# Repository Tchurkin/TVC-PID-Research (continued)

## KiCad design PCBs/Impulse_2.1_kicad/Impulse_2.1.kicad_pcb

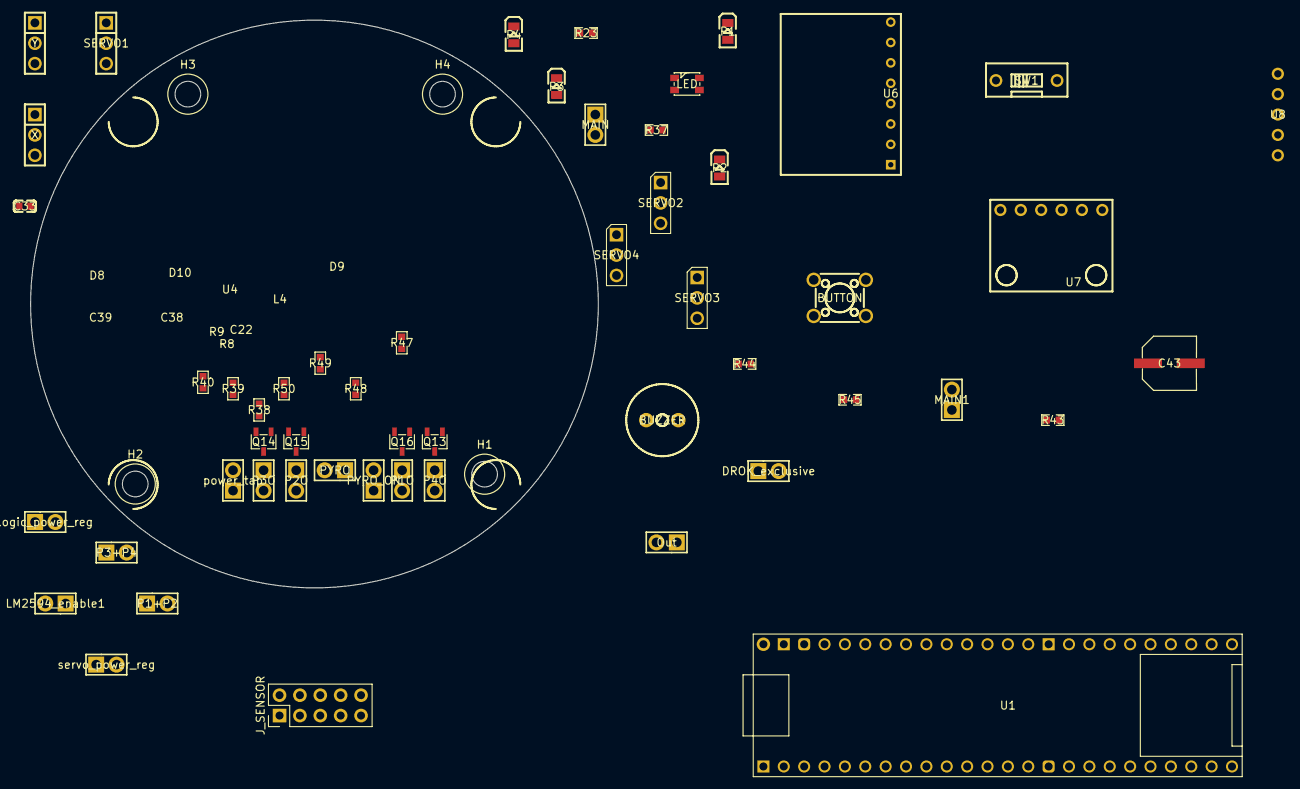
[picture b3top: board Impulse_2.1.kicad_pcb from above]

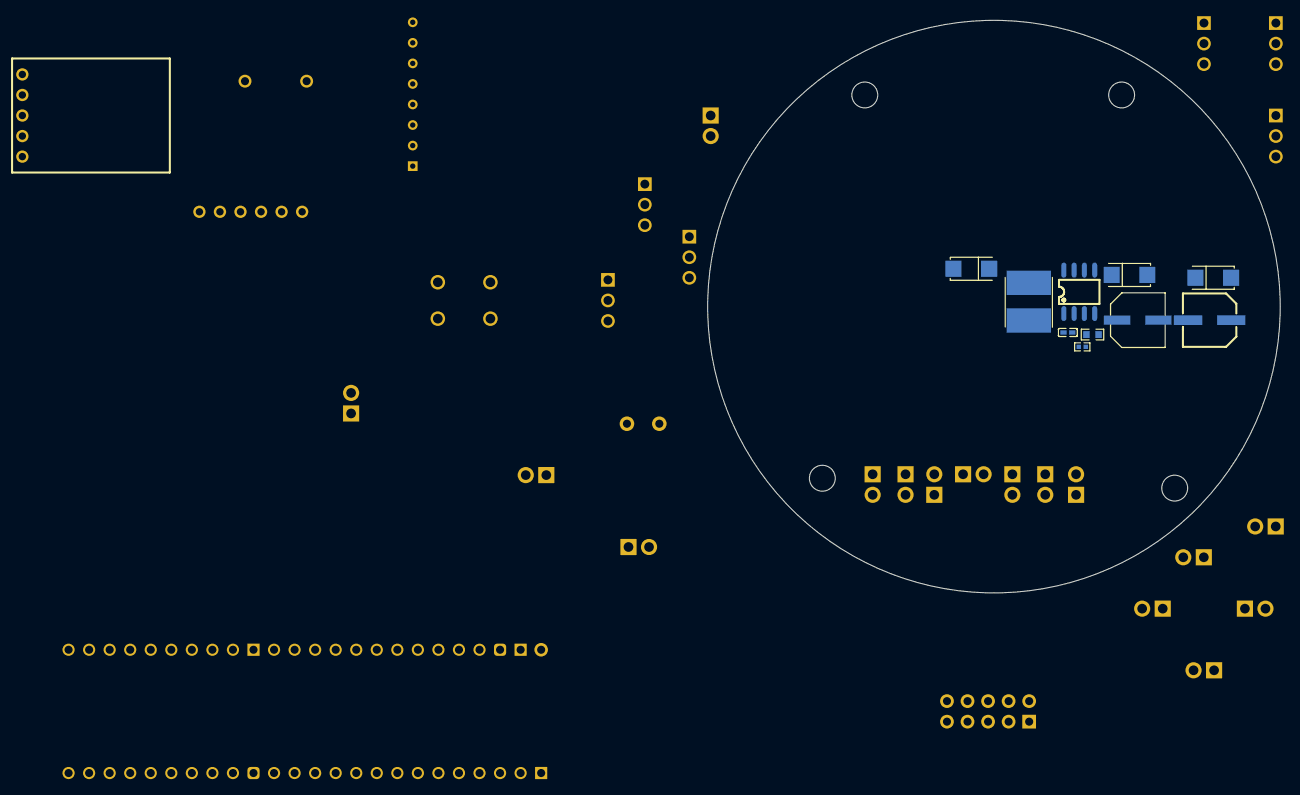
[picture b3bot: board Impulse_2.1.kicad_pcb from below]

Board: 2 copper layers, 70.8 x 70.8 mm, 67 parts (11 on the bottom side), 47 nets, no tracks yet.

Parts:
BUTTON: SW-TH_4P-L6.0-W6.0-P4.50-LS6.5
BUZZER: BUZ-TH_BD9.0-P4.00-D0.6-FD
C22: C0402
C33: C0603
C38: CAP-SMD_BD6.3-L6.6-W6.6-LS7.2-R-RD
C39: CAP-SMD_BD6.3-L6.5-W6.5-LS7.2-FD
C43: CAP-SMD_BD6.3-L6.6-W6.6-FD
D8, D9, D10: SMA_L4.3-W2.6-LS5.2-RD
DROK_exclusive: HDR-TH_2P-P2.54-V-M
H1, H2, H3, H4: MountingHole_3.2mm_M3
J_SENSOR: Header 2x5 sensor module; PinHeader_2x05_P2.54mm_Vertical
L4: IND-SMD_L5.8-W5.2
LED: LED-SMD_4P-L3.2-W2.8-LS3.5-BL-CW
LM2594_enable1: HDR-TH_2P-P2.54-V-M
MAIN, MAIN1: HDR-TH_2P-P2.54-V-M
Out: HDR-TH_2P-P2.54-V-M
P1, P2, P3, P4: LED0805-R-RD
P1+P2, P1O, P2O, P3+P4, P3O, P4O: HDR-TH_2P-P2.54-V-M
PYRO: HDR-TH_2P-P2.54-V-M
PYRO_ON: HDR-TH_2P-P2.54-V-M
Q13, Q14, Q15, Q16: SOT-23-3_L2.9-W1.6-P1.90-LS2.8-BR
R8: R0402
R9, R23, R37, R38, R39, R40, R43, R44, R45, R47, R48, R49, R50: R0603
SERVO1, SERVO2, SERVO3, SERVO4: HDR-TH_3P-P2.54-V-M
SW1: SW-TH_DSWB01LHGET
U1: TEENSY41
U4: SOP-8_L4.9-W3.9-P1.27-LS6.0-BL
U6: MPU-6050 MODULE
U7: BMP280
U8: BUCK CONVERTER-DROK
X: HDR-TH_3P-P2.54-V-M
Y: HDR-TH_3P-P2.54-V-M
logic_power_reg: HDR-TH_2P-P2.54-V-M
power_tap: HDR-TH_2P-P2.54-V-M
servo_power_reg: HDR-TH_2P-P2.54-V-M

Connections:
3.3V: BUTTON.1, J_SENSOR.1, LED.1, MAIN1.1, U1.3V3-1, U1.3V3-3, U6.1, U7.1
5V-CLEAN: C33.2, D8.1, DROK_exclusive.1, U1.VIN
5V-DIRTY: C43.1, D9.1, DROK_exclusive.2, SERVO1.2, SERVO2.2, SERVO3.2, SERVO4.2, X.2, Y.2
7.4V: P1O.2, P2O.2, P3O.2, P4O.2, PYRO_ON.1, power_tap.1
$1N14222: LED.3, R39.1
$1N14265: LED.4, R40.1
$1N14307: LED.2, R38.2
$1N14383: BUTTON.4, R23.2
$1N33864: C22.1, R8.1, R9.1, U4.4
$1N33870: D10.1, L4.1, U4.8
$1N42243: P1O.1, Q16.3, R37.1
$1N42245: P1.1, R37.2
$1N42393: P2O.1, Q15.3, R43.1
$1N42395: P2.1, R43.2
$1N42562: P3.1, R44.2
$1N49822: D9.2, U8.1, servo_power_reg.2
$1N50177: PYRO.1, PYRO_ON.2
$1N50225: MAIN.1, SW1.1
$1N50240: C39.1, SW1.2, U4.7, U8.4, logic_power_reg.1, servo_power_reg.1
$1N52582: D8.2, LM2594_enable1.2, logic_power_reg.2
$1N52591: C22.2, C38.1, L4.2, LM2594_enable1.1, R8.2
$1N56605: P4.1, R45.1
$1N56609: P4O.1, Q13.3, R45.2
$1N56715: P3O.1, Q14.3, R44.1
BUTTON: BUTTON.3, U1.14-A0/TX3/SPDIF_OUT
BUZZER: BUZZER.1, U1.13-SCK/LED
B_LED: R38.1, U1.8-TX2/IN2
CS_IMU: J_SENSOR.6, U1.0-RX1/CS1/CRX2
GND: BUZZER.2, C33.1, C38.2, C39.2, C43.2, D10.2, J_SENSOR.2, J_SENSOR.10, MAIN.2, MAIN1.2, P1.2, P2.2, P3.2, P4.2, PYRO.2, Q13.2, Q14.2, Q15.2, Q16.2, R9.2, R23.1, R47.2, R48.2, R49.2, R50.2, SERVO1.3, SERVO2.3, SERVO3.3, SERVO4.3, U1.GND1, U1.GND3, U1.GND6, U4.5, U4.6, U6.2, U7.2, U8.2, U8.3, X.3, Y.3, power_tap.2
G_LED: R39.2, U1.7-RX2/OUT1A
INT_IMU: J_SENSOR.7, U1.2-OUT2
MISO: J_SENSOR.5, U1.1-TX1/MISO1/CTX2
MOSI: J_SENSOR.4, U1.26-A12/MOSI1
PYRO1: P1+P2.1, Q16.1, R50.1, U1.9-OUT1C
PYRO2: P1+P2.2, Q15.1, R49.1, U1.10-CS\MQSR
PYRO3: P3+P4.1, Q14.1, R48.1, U1.11-MOSI/CTX1
PYRO4: P3+P4.2, Q13.1, R47.1, U1.12-MISO/MQSL
R_LED: R40.2, U1.6-OUT1D
SCK: J_SENSOR.3, U1.27-A13/SCK1
SCL: J_SENSOR.9, Out.2, U1.19-A5/SCL0, U6.3, U6.6, U7.3
SDA: J_SENSOR.8, Out.1, U1.18-A4/SDA0, U6.4, U6.5, U7.4
SERVO1: SERVO1.1, U1.5-IN2
SERVO2: SERVO2.1, U1.28-RX7
SERVO3: SERVO3.1, U1.29-TX7
SERVO4: SERVO4.1, U1.25-A11/RX6/SDA2
SERVOX: U1.3-LRCLK2, X.1
SERVOY: U1.4-BCLK2, Y.1

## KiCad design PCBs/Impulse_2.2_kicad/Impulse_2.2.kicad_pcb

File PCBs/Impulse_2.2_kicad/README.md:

# Impulse 2.2 — native KiCad rebuild

Clean-room rebuild of Impulse 2.1 (EasyEDA import) on **native KiCad libraries**. Same wiring,
same placement, same board outline — none of the conversion baggage (stranded silk, broken
annotation, pad-name mismatches).

- **Netlist verified identical** to Impulse 2.1 (183 connections, checked three ways: old PCB →
  new PCB → KiCad-exported schematic netlist). ERC: 0 violations.
- **Forward/back annotation works** — schematic and PCB are properly UUID-linked. "Update PCB
  from Schematic" is safe here (unlike 2.1).
- Unrouted (as was 2.1): DRC shows only ratsnest items + 6 courtyard overlaps from the packed
  import placement — re-place/route freely, silk moves with parts.
- Custom parts live in `Impulse22.pretty` / `Impulse22.kicad_sym` (Teensy 4.1 48-pin header
  footprint, 9mm/4.0mm-pitch buzzer).

## Deliberate changes vs 2.1
- Net renames for readability: `$1N50240`→`VBAT_SW`, `$1N52591`→`BUCK_5V`, `$1N33864`→`BUCK_FB`,
  `$1N33870`→`BUCK_SW`, `$1N50177`→`PYRO_ARM`, pyro channels→`PYROn_OUT`/`PYROn_LED`,
  RGB→`RGB_R/G/B`, etc.
- Ref renames (KiCad annotation needs a trailing digit): `X`→`X1`, `Y`→`Y1`, `PYRO`→`PYRO1`,
  `Out`→`OUT1`, `MAIN`→`BAT_MAIN1`, `MAIN1`→`AUX_3V3_1`, `LED`→`LED1`, `BUTTON`→`BUTTON1`,
  `BUZZER`→`BUZZER1`, `P1O`→`P1O1`, headers get a `1` suffix.
- `BUTTON` net merge: old nets `BUTTON` + `$1N14383` were one node through the switch's
  internally-bonded pins 3/4 — now a single `BUTTON` net on SW_PUSH pad pair 2.
- Teensy pads renamed to plain `0`–`41`, `VIN`, `3V3_1/2`, `GND1-3`.
- LED footprint pad numbering follows KiCad convention (1=K, 2=A — polarity preserved from 2.1).
- U4/LM2594 pinout verified against datasheet (4=FB, 7=VIN, 8=OUT; 5/6 both to GND).

## Schematic drawing style
The schematic **reproduces the hand-drawn Impulse 2.1 layout** — the 6 subsystem boxes and their
titles ("Voltage Regulator…", "Pyros and continuity check", "UI peripherals", "Servos (9 gram)",
"External Sensor Board", "Backup Sensors"), the original wires, and label placement — rebuilt with
native symbols. Where a native symbol's pin lands slightly off the old EasyEDA pin, a short stub
wire bridges it; only genuine cross-subsystem signals use labels (as in your original). Netlist
verified **byte-for-byte identical to the PCB** (183 connections, checked against KiCad's own
exporter). ERC: 0 errors, 67 warnings — all cosmetic (off-grid endpoints from the EasyEDA sub-grid,
lib-symbol-cache notes), same class the 2.1 import had.

Generators:
- `_gen_pcb.py` — reads `../Impulse_2.1_kicad/_inventory.json`, emits the native PCB.
- `_gen_sch2.py` — reads the PCB + the old schematic geometry, emits the layout-preserving sheet.
  (`_gen_sch.py` is the earlier grid-layout version, kept for reference.)
- `_patch_labels.py` — run AFTER `_gen_sch2.py`; uses KiCad's netlist as ground truth to drop a
  label on any pin a sub-grid stub missed (currently the 3 RGB-resistor pins).
- `_sym_uuids.json` links schematic symbols to PCB footprints; `_pin_nets.json` feeds the patcher.

Regen recipe: `python _gen_pcb.py && python _gen_sch2.py && python _patch_labels.py`

## Power redesign (2026-07-02)
Replaced the 150 kHz LM2594 circuit + DROK module + OR-diodes + 5 selector jumpers with two
1.1 MHz synchronous bucks (`_redesign_sch.py` / `_redesign_pcb.py`):
- **U2 = AP63205WU-7** (5 V / 2 A, TSOT-23-6) → `5V-CLEAN` (Teensy + sensors)
- **U3 = AP63305WU-7** (5 V / 3 A, same family/pinout — *verify pinout vs datasheet before fab*)
  → `SERVO_EN1` jumper → `5V-DIRTY` (servos)
- Each: 10 µF in (C1/C2), 100 nF BST (C3/C4), 6.8/4.7 µH SRN6045 (L1/L2), 2×22 µF out (C5–C8).
- **C10 = 220 µF** bulk on the pyro 7.4 V rail (was missing entirely).
- Jumpers kept: `PYRO_ON1` (pyro arming), `SERVO_EN1` (servo disable), SW1 master switch.
  Removed: `DROK_exclusive1` (bridged clean↔dirty!), `LM2594_enable1`, `logic_power_reg1`,
  `servo_power_reg1`, `power_tap1`.
- Net `Net-(SW1-B)` → `VBAT`. ERC 0/0; sch==pcb verified (204 connections).

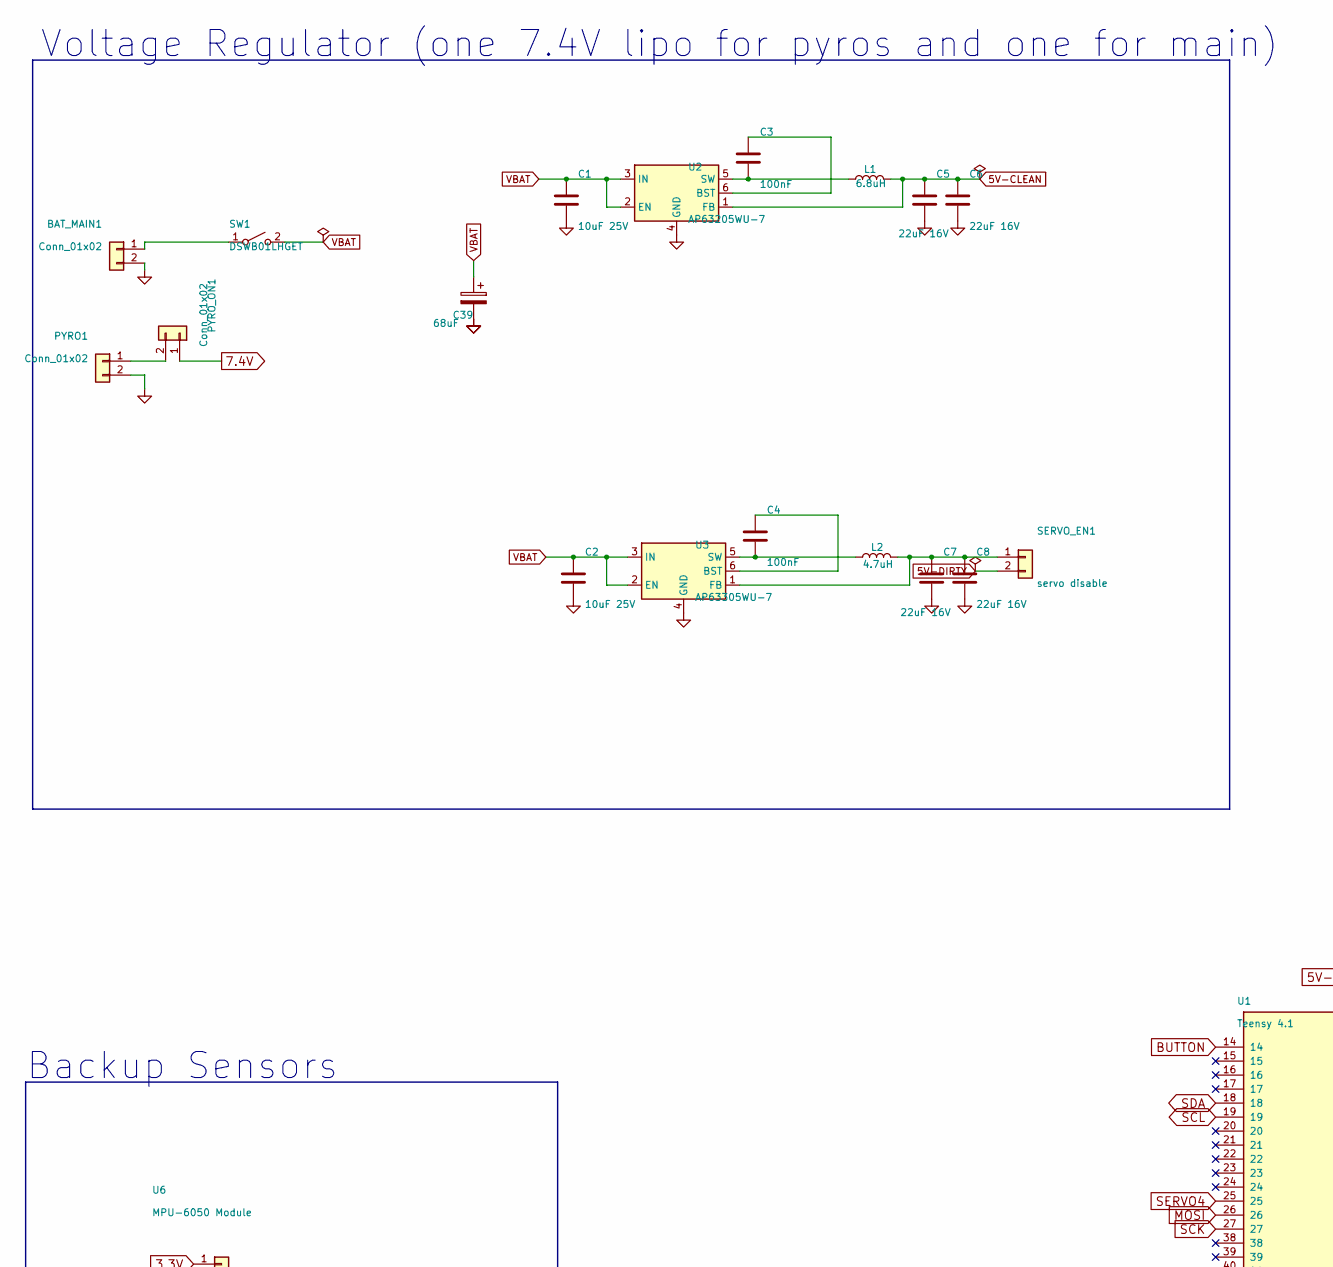
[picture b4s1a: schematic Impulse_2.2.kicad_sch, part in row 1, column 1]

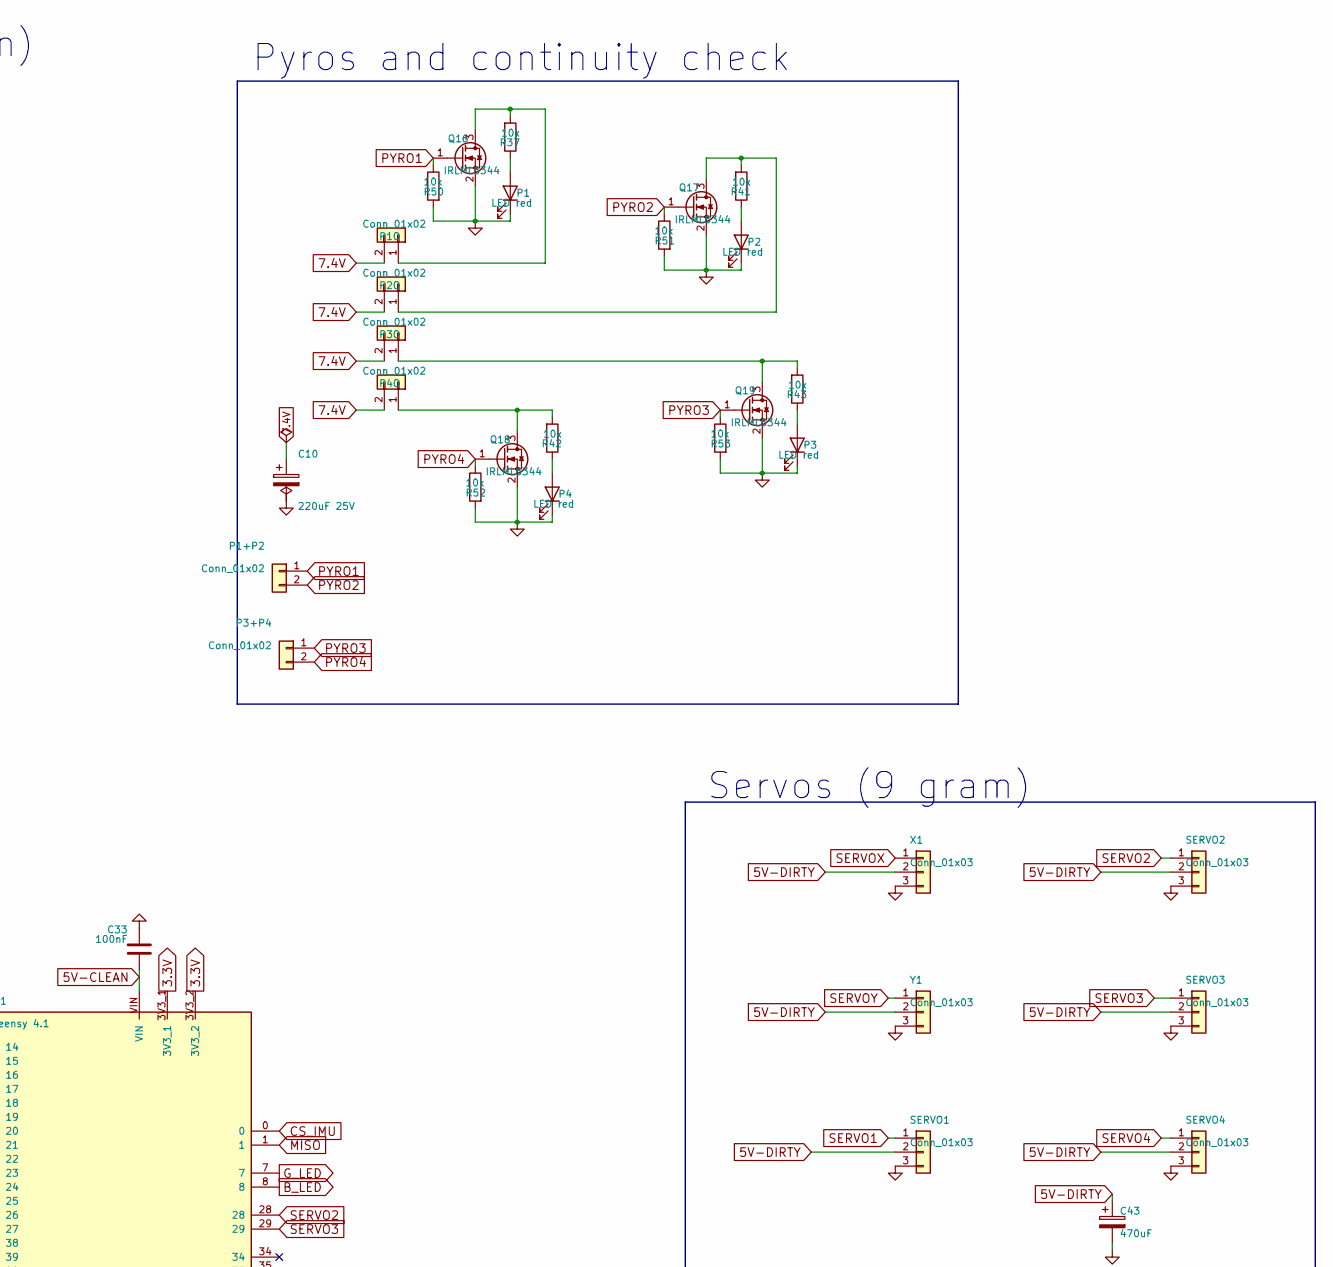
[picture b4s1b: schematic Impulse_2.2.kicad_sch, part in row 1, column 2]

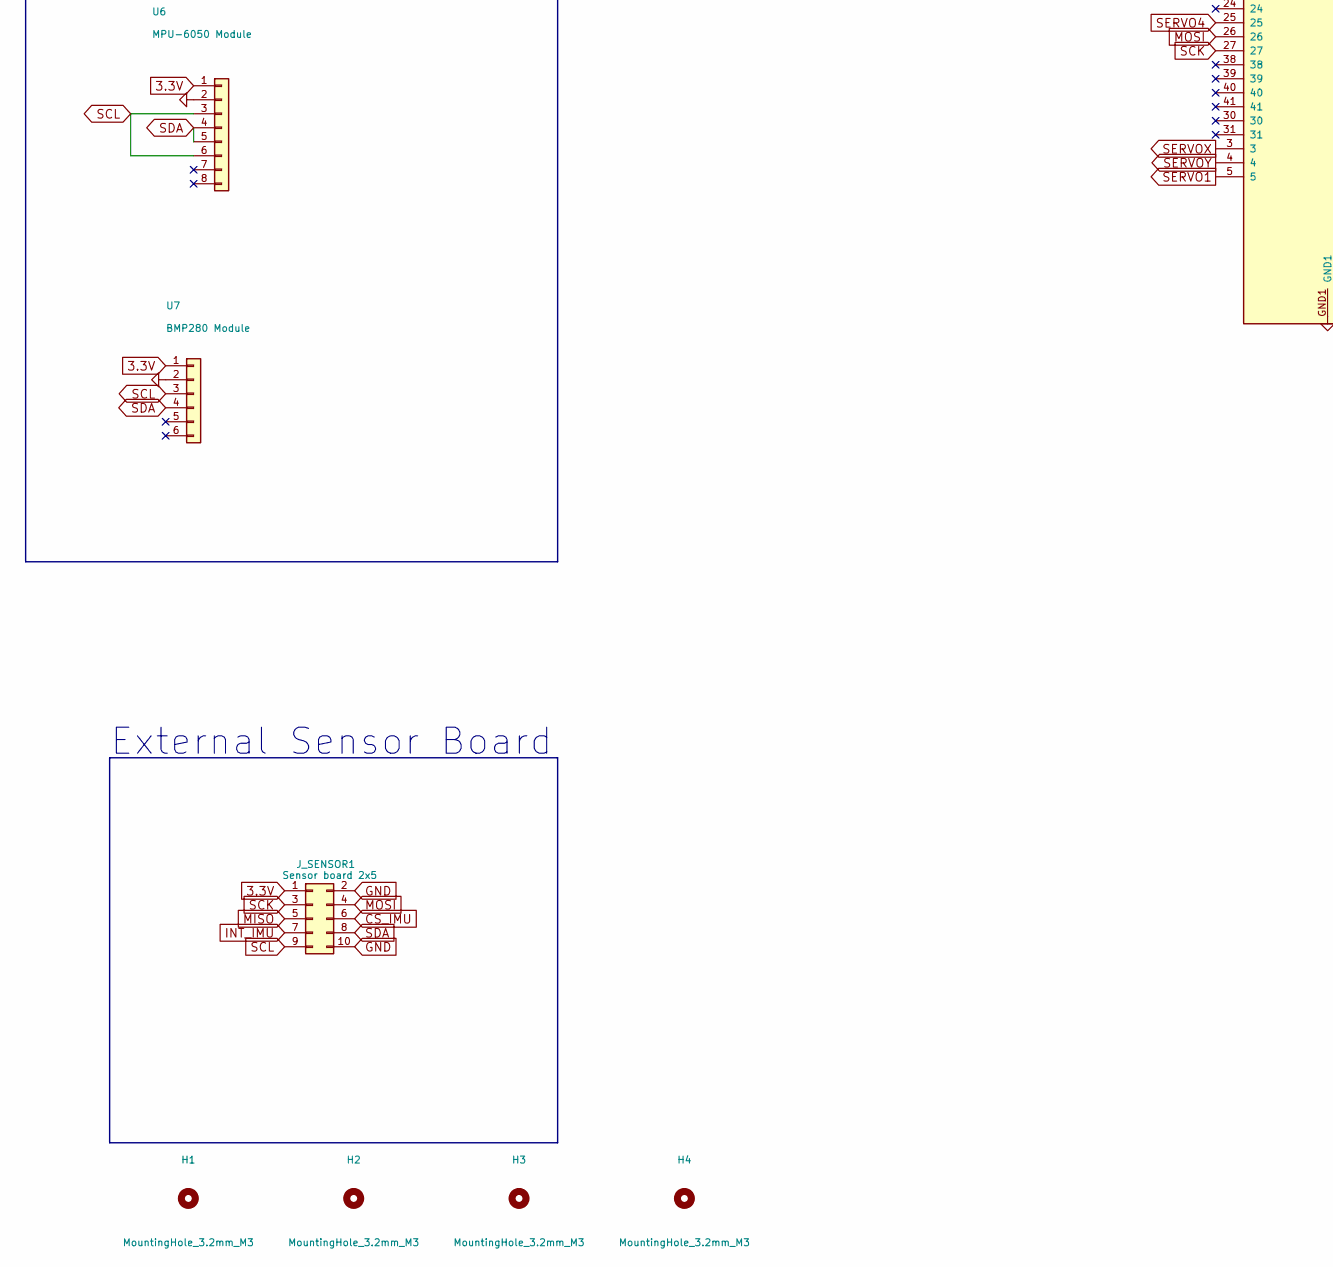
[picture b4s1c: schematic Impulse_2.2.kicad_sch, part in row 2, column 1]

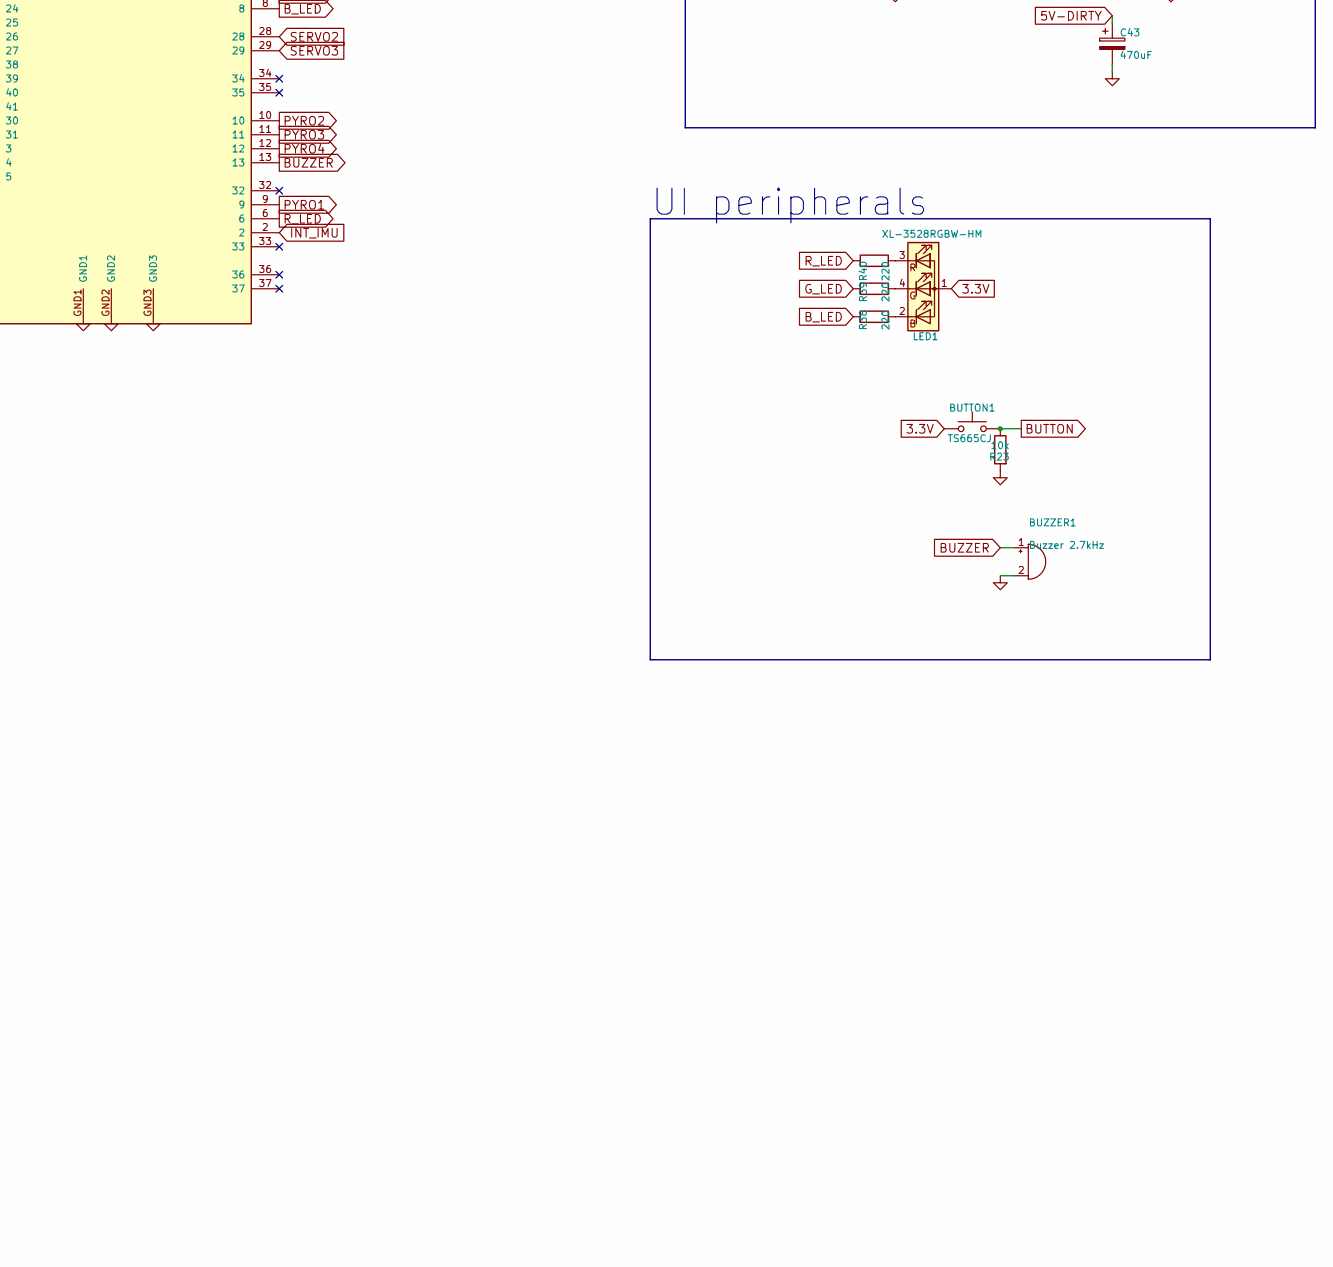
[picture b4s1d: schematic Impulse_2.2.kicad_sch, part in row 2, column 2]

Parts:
BAT_MAIN1: Conn_01x02; PinHeader_1x02_P2.54mm_Vertical
BUTTON1: TS665CJ; SW_PUSH_6mm
BUZZER1: Buzzer 2.7kHz; Buzzer_D9.0mm_P4.00mm
C1, C2: 10uF 25V; C_1206_3216Metric
C3, C4, C33: 100nF; C_0603_1608Metric
C5, C6, C7, C8: 22uF 16V; C_1206_3216Metric
C10: 220uF 25V; CP_Elec_8x10
C39: 68uF; CP_Elec_6.3x7.7
C43: 470uF; CP_Elec_6.3x7.7
H1, H2, H3, H4: MountingHole_3.2mm_M3
J_SENSOR1: Sensor board 2x5; PinHeader_2x05_P2.54mm_Vertical
L1: 6.8uH; L_Bourns_SRN6045TA
L2: 4.7uH; L_Bourns_SRN6045TA
LED1: XL-3528RGBW-HM; LED_RGB_Wuerth-PLCC4_3.2x2.8mm_150141M173100
P1, P2, P3, P4: LED red; LED_0805_2012Metric
P1+P2, P1O, P2O, P3+P4, P3O, P4O: Conn_01x02; PinHeader_1x02_P2.54mm_Vertical
PYRO1: Conn_01x02; PinHeader_1x02_P2.54mm_Vertical
PYRO_ON1: Conn_01x02; PinHeader_1x02_P2.54mm_Vertical
Q16, Q17, Q18, Q19: IRLML6344; SOT-23
R23, R37, R41, R42, R43, R50, R51, R52, R53: 10k; R_0603_1608Metric
R38, R39, R40: 220; R_0603_1608Metric
SERVO1, SERVO2, SERVO3, SERVO4: Conn_01x03; PinHeader_1x03_P2.54mm_Vertical
SERVO_EN1: servo disable; PinHeader_1x02_P2.54mm_Vertical
SW1: DSWB01LHGET; SW_DIP_SPSTx01_Slide_6.7x4.1mm_W7.62mm_P2.54mm_LowProfile
U1: Teensy 4.1; TEENSY41
U2: AP63205WU-7; TSOT-23-6
U3: AP63305WU-7; TSOT-23-6
U6: MPU-6050 Module; PinHeader_1x08_P2.54mm_Vertical
U7: BMP280 Module; PinHeader_1x06_P2.54mm_Vertical
X1: Conn_01x03; PinHeader_1x03_P2.54mm_Vertical
Y1: Conn_01x03; PinHeader_1x03_P2.54mm_Vertical

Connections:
3.3V: BUTTON1.1, J_SENSOR1.1, LED1.1 (A), U1.3V3_1, U1.3V3_2, U6.1, U7.1
5V-CLEAN: C5.1, C6.1, C33.2, L1.2, U1.VIN, U2.1 (FB)
5V-DIRTY: C43.1, SERVO1.2, SERVO2.2, SERVO3.2, SERVO4.2, SERVO_EN1.2, X1.2, Y1.2
7.4V: C10.1, P1O.2, P2O.2, P3O.2, P4O.2, PYRO_ON1.1
BUTTON: BUTTON1.2, R23.1, U1.14
BUZZER: BUZZER1.1 (+), U1.13
B_LED: R38.1, U1.8
CS_IMU: J_SENSOR1.6, U1.0
GND: BAT_MAIN1.2, BUZZER1.2 (-), C1.2, C2.2, C5.2, C6.2, C7.2, C8.2, C10.2, C33.1, C39.2, C43.2, J_SENSOR1.2, J_SENSOR1.10, P1.1 (K), P2.1 (K), P3.1 (K), P4.1 (K), PYRO1.2, Q16.2 (S), Q17.2 (S), Q18.2 (S), Q19.2 (S), R23.2, R50.2, R51.2, R52.2, R53.2, SERVO1.3, SERVO2.3, SERVO3.3, SERVO4.3, U1.GND1, U1.GND2, U1.GND3, U2.4 (GND), U3.4 (GND), U6.2, U7.2, X1.3, Y1.3
G_LED: R39.1, U1.7
INT_IMU: J_SENSOR1.7, U1.2
MISO: J_SENSOR1.5, U1.1
MOSI: J_SENSOR1.4, U1.26
unnamed: BAT_MAIN1.1, SW1.1 (A)
unnamed: LED1.2 (BK), R38.2
unnamed: LED1.4 (GK), R39.2
unnamed: LED1.3 (RK), R40.2
unnamed: P1.2 (A), R37.1
unnamed: P1O.1, Q16.3 (D), R37.2
unnamed: P2.2 (A), R41.1
unnamed: P2O.1, Q17.3 (D), R41.2
unnamed: P3.2 (A), R43.1
unnamed: P3O.1, Q19.3 (D), R43.2
unnamed: P4.2 (A), R42.1
unnamed: P4O.1, Q18.3 (D), R42.2
unnamed: PYRO1.1, PYRO_ON1.2
unnamed: C7.1, C8.1, L2.2, SERVO_EN1.1, U3.1 (FB)
unnamed: C3.1, U2.6 (BST)
unnamed: C3.2, L1.1, U2.5 (SW)
unnamed: C4.1, U3.6 (BST)
unnamed: C4.2, L2.1, U3.5 (SW)
PYRO1: P1+P2.1, Q16.1 (G), R50.1, U1.9
PYRO2: P1+P2.2, Q17.1 (G), R51.1, U1.10
PYRO3: P3+P4.1, Q19.1 (G), R53.1, U1.11
PYRO4: P3+P4.2, Q18.1 (G), R52.1, U1.12
R_LED: R40.1, U1.6
SCK: J_SENSOR1.3, U1.27
SCL: J_SENSOR1.9, U1.19, U6.3, U6.6, U7.3
SDA: J_SENSOR1.8, U1.18, U6.4, U6.5, U7.4
SERVO1: SERVO1.1, U1.5
SERVO2: SERVO2.1, U1.28
SERVO3: SERVO3.1, U1.29
SERVO4: SERVO4.1, U1.25
SERVOX: U1.3, X1.1
SERVOY: U1.4, Y1.1
VBAT: C1.1, C2.1, C39.1, SW1.2 (B), U2.2 (EN), U2.3 (IN), U3.2 (EN), U3.3 (IN)

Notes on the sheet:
Pyros and continuity check
Voltage Regulator (one 7.4V lipo for pyros and one for main)
UI peripherals
Servos (9 gram)
External Sensor Board
Backup Sensors

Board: 2 copper layers, 64 parts (13 on the bottom side), 46 nets, no tracks yet.

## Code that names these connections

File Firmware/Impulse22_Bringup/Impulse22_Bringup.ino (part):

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
  Pin map verified pad-by-pad against PCBs/Impulse_2.2_kicad/Impulse_2.2.kicad_pcb
  (2026-08-12). It is NOT the same as the old Sysiphus sketches: those use
  Serial1 for GPS (= pins 0/1 = CS_IMU/MISO here) and servo pin 2 (= INT_IMU).

  SENSORS
    Sensor board, SPI1 @ MOSI 26 / MISO 1 / SCK 27:
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#include <Adafruit_BMP280.h>

// ── Impulse 2.2 pin map ──────────────────────────────────────────────────────
constexpr int PIN_CS_IMU    = 0;    // SPI1 CS  -> ICM-42688-P
constexpr int PIN_INT_IMU   = 2;    // ICM-42688-P INT1
constexpr int PIN_RLED      = 6;    // RGB LED1 is COMMON ANODE to 5V-CLEAN:
constexpr int PIN_GLED      = 7;    //   drive LOW = on, HIGH = off
constexpr int PIN_BLED      = 8;
constexpr int PIN_PYRO[4]   = {9, 10, 11, 12};
constexpr int PIN_BUZZER    = 13;   // gate of Q22, active HIGH
constexpr int PIN_BUTTON    = 14;   // 10k pulldown R23, pressed = HIGH
constexpr int PIN_CS_BARO   = 15;   // SPI1 CS  -> DPS310
constexpr int PIN_GPS_PPS   = 20;
constexpr int PIN_VBAT_SENSE     = 21;
constexpr int PIN_SERVO_V_SENSE  = 22;
constexpr int PIN_PYRO_V_SENSE   = 23;
constexpr int PIN_MOSI1     = 26;
constexpr int PIN_SCK1      = 27;
constexpr int PIN_MISO1     = 1;
constexpr int PIN_SENS_DET  = 32;   // LOW = sensor-board harness present

#define GPS_SERIAL Serial4          // NOT Serial1 — pins 0/1 are CS_IMU/MISO
constexpr uint32_t GPS_BAUD = 9600;

// Divider ratios from the schematic: Vrail = Vpin / ratio
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  digitalWrite(PIN_GLED, !g);
  digitalWrite(PIN_BLED, !b);
}
void beep(int freq, int dur) { tone(PIN_BUZZER, freq); delay(dur); noTone(PIN_BUZZER); }

// Returns 0 = not pressed, 1 = short press, 2 = long press (>1 s)
int readButton() {
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//  ICM-42688-P
// ─────────────────────────────────────────────────────────────────────────────
bool icmBegin() {
  spiWriteReg(PIN_CS_IMU, ICM_SPI, ICM_DEVICE_CONFIG, 0x01);   // soft reset
  delay(5);

  uint8_t who = spiReadReg(PIN_CS_IMU, ICM_SPI, ICM_WHO_AM_I);
  if (who != ICM_WHOAMI_EXPECT) {
    snprintf(diag, sizeof diag, "WHO_AM_I = 0x%02X, expected 0x47%s", who,
             who == 0xFF ? "  (MISO floating / not connected?)"
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
  // Pin 9 of the LGA is unused here; lock the interface to SPI so a floating
  // I2C pad can never put the part into I2C mode mid-flight.
  uint8_t intf = spiReadReg(PIN_CS_IMU, ICM_SPI, ICM_INTF_CONFIG0);
  spiWriteReg(PIN_CS_IMU, ICM_SPI, ICM_INTF_CONFIG0, (intf & 0xFC) | 0x03);  // UI_SIFS_CFG = disable I2C

  spiWriteReg(PIN_CS_IMU, ICM_SPI, ICM_GYRO_CONFIG0,  (0x00 << 5) | 0x06);   // ±2000 dps, 1 kHz
  spiWriteReg(PIN_CS_IMU, ICM_SPI, ICM_ACCEL_CONFIG0, (0x00 << 5) | 0x06);   // ±16 g,     1 kHz
  spiWriteReg(PIN_CS_IMU, ICM_SPI, ICM_PWR_MGMT0, 0x0F);                     // gyro + accel low-noise
  delay(50);                                                                 // gyro start-up
  return true;
}
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// ax/ay/az in g, gx/gy/gz in dps, temp in degC
void icmRead(float& ax, float& ay, float& az, float& gx, float& gy, float& gz, float& tempC) {
  uint8_t b[14];
  spiReadBurst(PIN_CS_IMU, ICM_SPI, ICM_TEMP_DATA1, b, 14);
  int16_t t  = (int16_t)((b[0]  << 8) | b[1]);
  int16_t rx = (int16_t)((b[2]  << 8) | b[3]);
  int16_t ry = (int16_t)((b[4]  << 8) | b[5]);
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//  DPS310
// ─────────────────────────────────────────────────────────────────────────────
bool dpsBegin() {
  spiWriteReg(PIN_CS_BARO, DPS_SPI, DPS_RESET, 0x89);          // soft reset
  delay(50);

  uint8_t id = spiReadReg(PIN_CS_BARO, DPS_SPI, DPS_PROD_ID);
  if (id != DPS_ID_EXPECT) {
    snprintf(diag, sizeof diag, "PROD_ID = 0x%02X, expected 0x10%s", id,
             (id == 0xFF || id == 0x00) ? "  (check CS_BARO, harness pin 5)" : "");
    return false;
  }

  // Wait for the trim/coefficients to load out of OTP.
  uint32_t t0 = millis();
  while (!(spiReadReg(PIN_CS_BARO, DPS_SPI, DPS_MEAS_CFG) & 0xC0)) {   // SENSOR_RDY | COEF_RDY
    if (millis() - t0 > 500) {
      snprintf(diag, sizeof diag, "timeout waiting for SENSOR_RDY|COEF_RDY");
      return false;
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
  // Infineon errata workaround: the OTP read must be re-triggered once after
  // reset or the temperature coefficients come back wrong on some lots.
  spiWriteReg(PIN_CS_BARO, DPS_SPI, 0x0E, 0xA5);
  spiWriteReg(PIN_CS_BARO, DPS_SPI, 0x0F, 0x96);
  spiWriteReg(PIN_CS_BARO, DPS_SPI, 0x62, 0x02);
  spiWriteReg(PIN_CS_BARO, DPS_SPI, 0x0E, 0x00);
  spiWriteReg(PIN_CS_BARO, DPS_SPI, 0x0F, 0x00);

  uint8_t c[18];
  spiReadBurst(PIN_CS_BARO, DPS_SPI, DPS_COEF, c, 18);
  dpsCoef.c0  = signExtend(((uint32_t)c[0] << 4) | (c[1] >> 4), 12);
  dpsCoef.c1  = signExtend((((uint32_t)c[1] & 0x0F) << 8) | c[2], 12);
  dpsCoef.c00 = signExtend(((uint32_t)c[3] << 12) | ((uint32_t)c[4] << 4) | (c[5] >> 4), 20);
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  dpsCoef.c30 = signExtend(((uint32_t)c[16] << 8) | c[17], 16);

  // TMP_EXT must match the source the coefficients were trimmed against.
  uint8_t srce = spiReadReg(PIN_CS_BARO, DPS_SPI, DPS_COEF_SRCE) & 0x80;
  spiWriteReg(PIN_CS_BARO, DPS_SPI, DPS_PRS_CFG, 0x53);          // 32 Hz, 8x oversample
  spiWriteReg(PIN_CS_BARO, DPS_SPI, DPS_TMP_CFG, srce | 0x50);   // 32 Hz, 1x oversample
  spiWriteReg(PIN_CS_BARO, DPS_SPI, DPS_CFG_REG, 0x00);          // no shift needed at <=8x
  spiWriteReg(PIN_CS_BARO, DPS_SPI, DPS_MEAS_CFG, 0x07);         // continuous pressure + temp
  delay(50);
  return true;
}

void dpsRead(float& hPa, float& tempC, float& altM) {
  uint8_t b[6];
  spiReadBurst(PIN_CS_BARO, DPS_SPI, DPS_PSR_B2, b, 6);
  int32_t praw = signExtend(((uint32_t)b[0] << 16) | ((uint32_t)b[1] << 8) | b[2], 24);
  int32_t traw = signExtend(((uint32_t)b[3] << 16) | ((uint32_t)b[4] << 8) | b[5], 24);

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// WHO_AM_I answering — so they look present while streaming sentinel values.
// Detect the recovery edge and re-run the init that the glitch threw away.
void checkBrownout() {
  bool up = (readRail(PIN_VBAT_SENSE, VBAT_RATIO) >= 6.0f);
  if (up && !railWasUp && railSeenUp) {
    brownouts++;
    Serial.print(F("  [VBAT dropped and recovered — brownout #"));
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}

void printRails() {
  Serial.print(F("  VBAT      ")); Serial.print(readRail(PIN_VBAT_SENSE, VBAT_RATIO), 2);
  Serial.print(F(" V   |  5V-DIRTY ")); Serial.print(readRail(PIN_SERVO_V_SENSE, SERVO_RATIO), 2);
  Serial.print(F(" V   |  7.4V pyro ")); Serial.print(readRail(PIN_PYRO_V_SENSE, PYRO_RATIO), 2);
  Serial.print(F(" V"));
  if (brownouts) { Serial.print(F("   [brownouts: ")); Serial.print(brownouts); Serial.print(F("]")); }
  Serial.println();
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  // is running on leakage through its own SPI pins' ESD clamps — those chips
  // work down to 1.7 V, so they will happily return good-looking data that
  // proves nothing about the board.
  float vbat  = readRail(PIN_VBAT_SENSE, VBAT_RATIO);
  float vserv = readRail(PIN_SERVO_V_SENSE, SERVO_RATIO);
  bool powered = (vbat >= 6.0f);

  // Every rail number above is measured against the Teensy's own 3.3 V rail as
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    Serial.println(F("       1. U3 genuinely out of regulation"));
    Serial.println(F("       2. Teensy 3.3 V (the ADC reference) sagging — but then"));
    Serial.println(F("          VBAT and 7.4V scale by the same factor, so check those"));
    Serial.println(F("       3. leakage on the SERVO_V_SENSE node (pin 22 / R56 / R57),"));
    Serial.println(F("          which drags this reading alone and leaves the others right"));
    Serial.println(F("     On THIS board (2026-08-12) it was #3: meter said 4.95 V while"));
    Serial.println(F("     the ADC said 3.60 V. Verify with a meter before believing this."));
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    Serial.println(F("  *****************************************************"));
  }

  Serial.print(F("\n  SENS_DET (pin 32): "));
  if (!powered) {
    Serial.println(F("unreadable — pull-up comes from 5V-CLEAN, which is dead"));
  } else {
    Serial.println(digitalRead(PIN_SENS_DET) == LOW
                   ? F("LOW  -> sensor-board harness CONNECTED")
                   : F("HIGH -> harness NOT detected"));
  }
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
  pinMode(PIN_RLED, OUTPUT); pinMode(PIN_GLED, OUTPUT); pinMode(PIN_BLED, OUTPUT);
  LED(false, false, false);
  pinMode(PIN_BUZZER, OUTPUT);
  pinMode(PIN_BUTTON, INPUT);          // external 10k pulldown, do NOT use INPUT_PULLUP
  pinMode(PIN_SENS_DET, INPUT);        // driven by the LED4 string, no pullup
  pinMode(PIN_INT_IMU, INPUT);
  pinMode(PIN_GPS_PPS, INPUT);
  pinMode(PIN_CS_IMU, OUTPUT);  digitalWrite(PIN_CS_IMU, HIGH);
  pinMode(PIN_CS_BARO, OUTPUT); digitalWrite(PIN_CS_BARO, HIGH);

  analogReadResolution(ADC_BITS);
  attachInterrupt(digitalPinToInterrupt(PIN_GPS_PPS), ppsISR, RISING);
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
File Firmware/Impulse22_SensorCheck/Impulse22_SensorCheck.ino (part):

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#include <math.h>

// ── Impulse 2.2 pin map ──────────────────────────────────────────────────────
constexpr int PIN_CS_IMU  = 0,  PIN_CS_BARO = 15;
constexpr int PIN_MISO1   = 1,  PIN_MOSI1   = 26, PIN_SCK1 = 27;
constexpr int PIN_PYRO[4] = {9, 10, 11, 12};
constexpr int PIN_RLED    = 6,  PIN_GLED    = 7,  PIN_BLED = 8;
constexpr int PIN_BUZZER  = 13, PIN_BUTTON  = 14;
constexpr int PIN_GPS_PPS = 20;
constexpr int PIN_MAIN_LED = 30, PIN_PYRO_LED = 31;   // active HIGH
#define GPS_SERIAL Serial4                            // NOT Serial1: pins 0/1 are CS_IMU/MISO
constexpr uint32_t GPS_BAUD = 9600;

SPISettings ICM_CFG(8000000, MSBFIRST, SPI_MODE0);
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
// ── ICM-42688-P ──────────────────────────────────────────────────────────────
bool icmBegin(){
  wr(PIN_CS_IMU,ICM_CFG,0x11,0x01); delay(5);            // soft reset
  if(rd(PIN_CS_IMU,ICM_CFG,0x75) != 0x47) return false;  // WHO_AM_I
  uint8_t itf = rd(PIN_CS_IMU,ICM_CFG,0x4C);
  wr(PIN_CS_IMU,ICM_CFG,0x4C,(itf&0xFC)|0x03);           // lock to SPI
  wr(PIN_CS_IMU,ICM_CFG,0x4F,0x06);                      // gyro  ±2000 dps, 1 kHz
  wr(PIN_CS_IMU,ICM_CFG,0x50,0x06);                      // accel ±16 g,     1 kHz
  wr(PIN_CS_IMU,ICM_CFG,0x4E,0x0F);                      // both low-noise
  delay(50);
  return true;
}
bool icmRead(float&ax,float&ay,float&az,float&gx,float&gy,float&gz,float&tc){
  uint8_t b[14]; rdN(PIN_CS_IMU,ICM_CFG,0x1D,b,14);
  int16_t t =(int16_t)((b[0]<<8)|b[1]);
  int16_t rx=(int16_t)((b[2]<<8)|b[3]),  ry=(int16_t)((b[4]<<8)|b[5]),  rz=(int16_t)((b[6]<<8)|b[7]);
  int16_t px=(int16_t)((b[8]<<8)|b[9]),  py=(int16_t)((b[10]<<8)|b[11]),pz=(int16_t)((b[12]<<8)|b[13]);
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struct { int32_t c0,c1,c00,c10,c01,c11,c20,c21,c30; } C;
constexpr float KP = 7864320.0f, KT = 524288.0f;         // 8x / 1x oversampling
bool dpsBegin(){
  wr(PIN_CS_BARO,DPS_CFG,0x0C,0x89); delay(50);          // soft reset
  if(rd(PIN_CS_BARO,DPS_CFG,0x0D) != 0x10) return false; // PROD_ID
  uint32_t t0=millis();
  while(!(rd(PIN_CS_BARO,DPS_CFG,0x08)&0xC0)){ if(millis()-t0>500) return false; delay(5); }
  // Infineon errata: re-trigger the OTP read or some lots return wrong temp coefficients.
  wr(PIN_CS_BARO,DPS_CFG,0x0E,0xA5); wr(PIN_CS_BARO,DPS_CFG,0x0F,0x96);
  wr(PIN_CS_BARO,DPS_CFG,0x62,0x02);
  wr(PIN_CS_BARO,DPS_CFG,0x0E,0x00); wr(PIN_CS_BARO,DPS_CFG,0x0F,0x00);
  uint8_t c[18]; rdN(PIN_CS_BARO,DPS_CFG,0x10,c,18);
  C.c0 =sxt(((uint32_t)c[0]<<4)|(c[1]>>4),12);
  C.c1 =sxt((((uint32_t)c[1]&0x0F)<<8)|c[2],12);
  C.c00=sxt(((uint32_t)c[3]<<12)|((uint32_t)c[4]<<4)|(c[5]>>4),20);
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  C.c01=sxt(((uint32_t)c[8]<<8)|c[9],16);   C.c11=sxt(((uint32_t)c[10]<<8)|c[11],16);
  C.c20=sxt(((uint32_t)c[12]<<8)|c[13],16); C.c21=sxt(((uint32_t)c[14]<<8)|c[15],16);
  C.c30=sxt(((uint32_t)c[16]<<8)|c[17],16);
  uint8_t srce = rd(PIN_CS_BARO,DPS_CFG,0x28)&0x80;
  wr(PIN_CS_BARO,DPS_CFG,0x06,0x53);                     // pressure 32 Hz, 8x
  wr(PIN_CS_BARO,DPS_CFG,0x07,srce|0x50);                // temp     32 Hz, 1x
  wr(PIN_CS_BARO,DPS_CFG,0x09,0x00);
  wr(PIN_CS_BARO,DPS_CFG,0x08,0x07);                     // continuous
  delay(50);
  return true;
}
void dpsRead(float&pa, float&tc){
  uint8_t b[6]; rdN(PIN_CS_BARO,DPS_CFG,0x00,b,6);
  float psc = sxt(((uint32_t)b[0]<<16)|((uint32_t)b[1]<<8)|b[2],24)/KP;
  float tsc = sxt(((uint32_t)b[3]<<16)|((uint32_t)b[4]<<8)|b[5],24)/KT;
  pa = C.c00 + psc*(C.c10 + psc*(C.c20 + psc*C.c30)) + tsc*C.c01 + tsc*psc*(C.c11 + psc*C.c21);
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  if(g){pinMode(PIN_GLED,OUTPUT);digitalWrite(PIN_GLED,LOW);}else pinMode(PIN_GLED,INPUT);
  if(b){pinMode(PIN_BLED,OUTPUT);digitalWrite(PIN_BLED,LOW);}else pinMode(PIN_BLED,INPUT);
}
void beep(int f,int d){ tone(PIN_BUZZER,f); delay(d); noTone(PIN_BUZZER); }

float groundPa = 0;
void zeroBaro(){ float pa,tc; dpsRead(pa,tc); groundPa = pa; }
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void setup(){
  for(int i=0;i<4;i++){ pinMode(PIN_PYRO[i],OUTPUT); digitalWrite(PIN_PYRO[i],LOW); }
  pinMode(PIN_RLED,OUTPUT); pinMode(PIN_GLED,OUTPUT); pinMode(PIN_BLED,OUTPUT); LED(false,false,false);
  pinMode(PIN_MAIN_LED,OUTPUT); digitalWrite(PIN_MAIN_LED,LOW);
  pinMode(PIN_PYRO_LED,OUTPUT); digitalWrite(PIN_PYRO_LED,LOW);
  pinMode(PIN_BUZZER,OUTPUT);
  pinMode(PIN_BUTTON,INPUT);                             // external 10k pulldown
  pinMode(PIN_GPS_PPS,INPUT);
  pinMode(PIN_CS_IMU,OUTPUT);  digitalWrite(PIN_CS_IMU,HIGH);
  pinMode(PIN_CS_BARO,OUTPUT); digitalWrite(PIN_CS_BARO,HIGH);
  attachInterrupt(digitalPinToInterrupt(PIN_GPS_PPS), ppsISR, RISING);

  Serial.begin(115200);
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  if(millis()-last < 250) return;
  last = millis();

  digitalWrite(PIN_MAIN_LED, haveICM && haveDPS);        // green  = SPI sensors alive
  digitalWrite(PIN_PYRO_LED, gpsHasFix);                 // yellow = GPS fix

  if(haveICM){
    float ax,ay,az,gx,gy,gz,tc;
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
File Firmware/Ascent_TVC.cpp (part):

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
// -- Pins (verify against your wiring) ----------------------------------------
constexpr int BUTTON = 14;
constexpr int BUZZER = 13;
constexpr int P1     = 9;    // LANDING LEGS deploy (melt wire) -- protects the TVC on touchdown
constexpr int P2     = 10;   // not connected
constexpr int P3     = 11;   // ASCENT motor ignition
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void LED(bool r,bool g,bool b){ digitalWrite(RLED,!r); digitalWrite(GLED,!g); digitalWrite(BLED,!b); }
void beep(int f,int d){ tone(BUZZER,f); delay(d); noTone(BUZZER); }
void writeServos(float sx,float sy){                    // clamp to a valid servo range for safety
  servoX.write((int)constrain(SERVO_X_SIGN*sx + 90 + XTUNE, 0, 180));
  servoY.write((int)constrain(SERVO_Y_SIGN*sy + 90 + YTUNE, 0, 180));
}
void neutralServos(){ servoX.write((int)(90+XTUNE)); servoY.write((int)(90+YTUNE)); }

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
// -- Setup ---------------------------------------------------------------------
void setup(){
  pinMode(BUTTON,INPUT); pinMode(BUZZER,OUTPUT);
  pinMode(RLED,OUTPUT); pinMode(GLED,OUTPUT); pinMode(BLED,OUTPUT);
  pinMode(P1,OUTPUT); pinMode(P2,OUTPUT); pinMode(P3,OUTPUT); pinMode(P4,OUTPUT);
  digitalWrite(P1,LOW); digitalWrite(P2,LOW); digitalWrite(P3,LOW); digitalWrite(P4,LOW);
  servoX.attach(SERVO_X_PIN); servoY.attach(SERVO_Y_PIN);
  neutralServos();
  LED(false,false,false);
  Serial.begin(115200); Wire.begin();
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
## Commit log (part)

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2026-04-26 Updated Aero Modelling and Shifted Research Direction
2026-04-29 AI Control
2026-05-03 paper direction updates
2026-05-28 Refine research framing: market relevance and joint-aware justification
2026-05-31 Reframe as bench-calibrated preflight tool; add experiments, bench tooling, firmware characterization
    - New framing: 'Replacing tune-until-it-flies with measure, verify, tune'
    - README, paper draft, mentor summary rewritten in builder voice
    - experiments/: validator calibration, scaling law, s2r ablation,
    p-estimation error, basic-vs-better sim, firmware audit, head-to-head,
    preflight workflow + phase diagram + current-vs-proposed figures
    - tools/: bench_to_validator, bench_to_autotune, gimbal bench parser
2026-06-02 New framing as tvc rocket and simulation failure regimes
2026-06-03 Remove stale MATLAB direction experiments
    Direction_B_RC_ADRC_PathFollow and ModelRocket_Adaptive_TVC outputs/data
    are superseded by the Python simulator rebuild. ModelRocket_Adaptive_TVC
    source files (src/, DEV_LOG.md) are retained for reference.
2026-06-03 Add Python simulator, Exp1/4/5 pipeline, and analysis tools
    Complete rebuild of TVC simulator in Python (sim/), replacing MATLAB.
    Adds Exp1 regime mapping (N=1200), Exp4 fidelity ablation (7 modules,
    3 seeds), Exp5 design-space gradient field (multi-seed, range-scaled),
    and fidelity dominance analysis tools.
    Key changes:
    - sim/: 13-module Python simulator; all 10 validation tests pass
2026-06-03 Update Exp5 to 3-seed gradients; regenerate figures; update docs
    - exp5_gradient_field_py.csv regenerated with EXP5_N_SEEDS_GRAD=3
    servo_slew: 42.1% → 25.3% (single-seed noise confirmed, not signal)
    Cm_alpha: 10.3% → 16.5%; Iyy enters top-3 at 13.9%
    - Exp5 figures (bottleneck, diminishing_returns, evolution_paths) regenerated
    - CLAUDE.md: added quantified mismatch numbers, updated Exp5 confidence levels,
    annotated rejected claims, documented open questions with current answers
2026-06-03 Add exp4simple paired run; extend Exp4A audit with confusion matrix
    - run_exp4simple(): new paired simple-vs-full comparison for all 1200 designs
    FidelityConfig.simple() vs FidelityConfig.full(), 3 seeds each (~40s runtime)
    - Key finding: INFEASIBLE false approval rate = 99.6%; FRAGILE = coin flip (50.3%)
    Simple model is systematically optimistic; zero false rejections in any regime
    - exp4a_decision_audit.py: added load_paired_data(), table_simple_vs_full(),
    fig_simple_confusion(); now [4/4] figures including confusion matrix
